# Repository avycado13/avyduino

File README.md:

# Avyduino

My take on the classic Arduino UNO. Powered by the same chips, but using a USB-C socket.

## Features
- USB-C
- Exact same pinout as classic Arduino UNO
- Power input switching
- Easy to solder components

## BOM
**FORGE REVIEWERS PLEASE ACTUALLY USE MY CSV**
I compiled 2 BOMs. One is from octopart and has parts sourced from multiple separate suppliers. [BOM here](ordering/bom.xlsx) and one entirely from LCSC. [BOM here](ordering/bom_lcsc_only.xlsx)

## Firmware
See [firmware/README.md](firmware/README.md) for the Uno Optiboot first-flash procedure and a USB serial bring-up sketch. The ATmega328P uses the standard Arduino Uno bootloader; the CH340G is a USB-to-UART bridge and does not need custom firmware.

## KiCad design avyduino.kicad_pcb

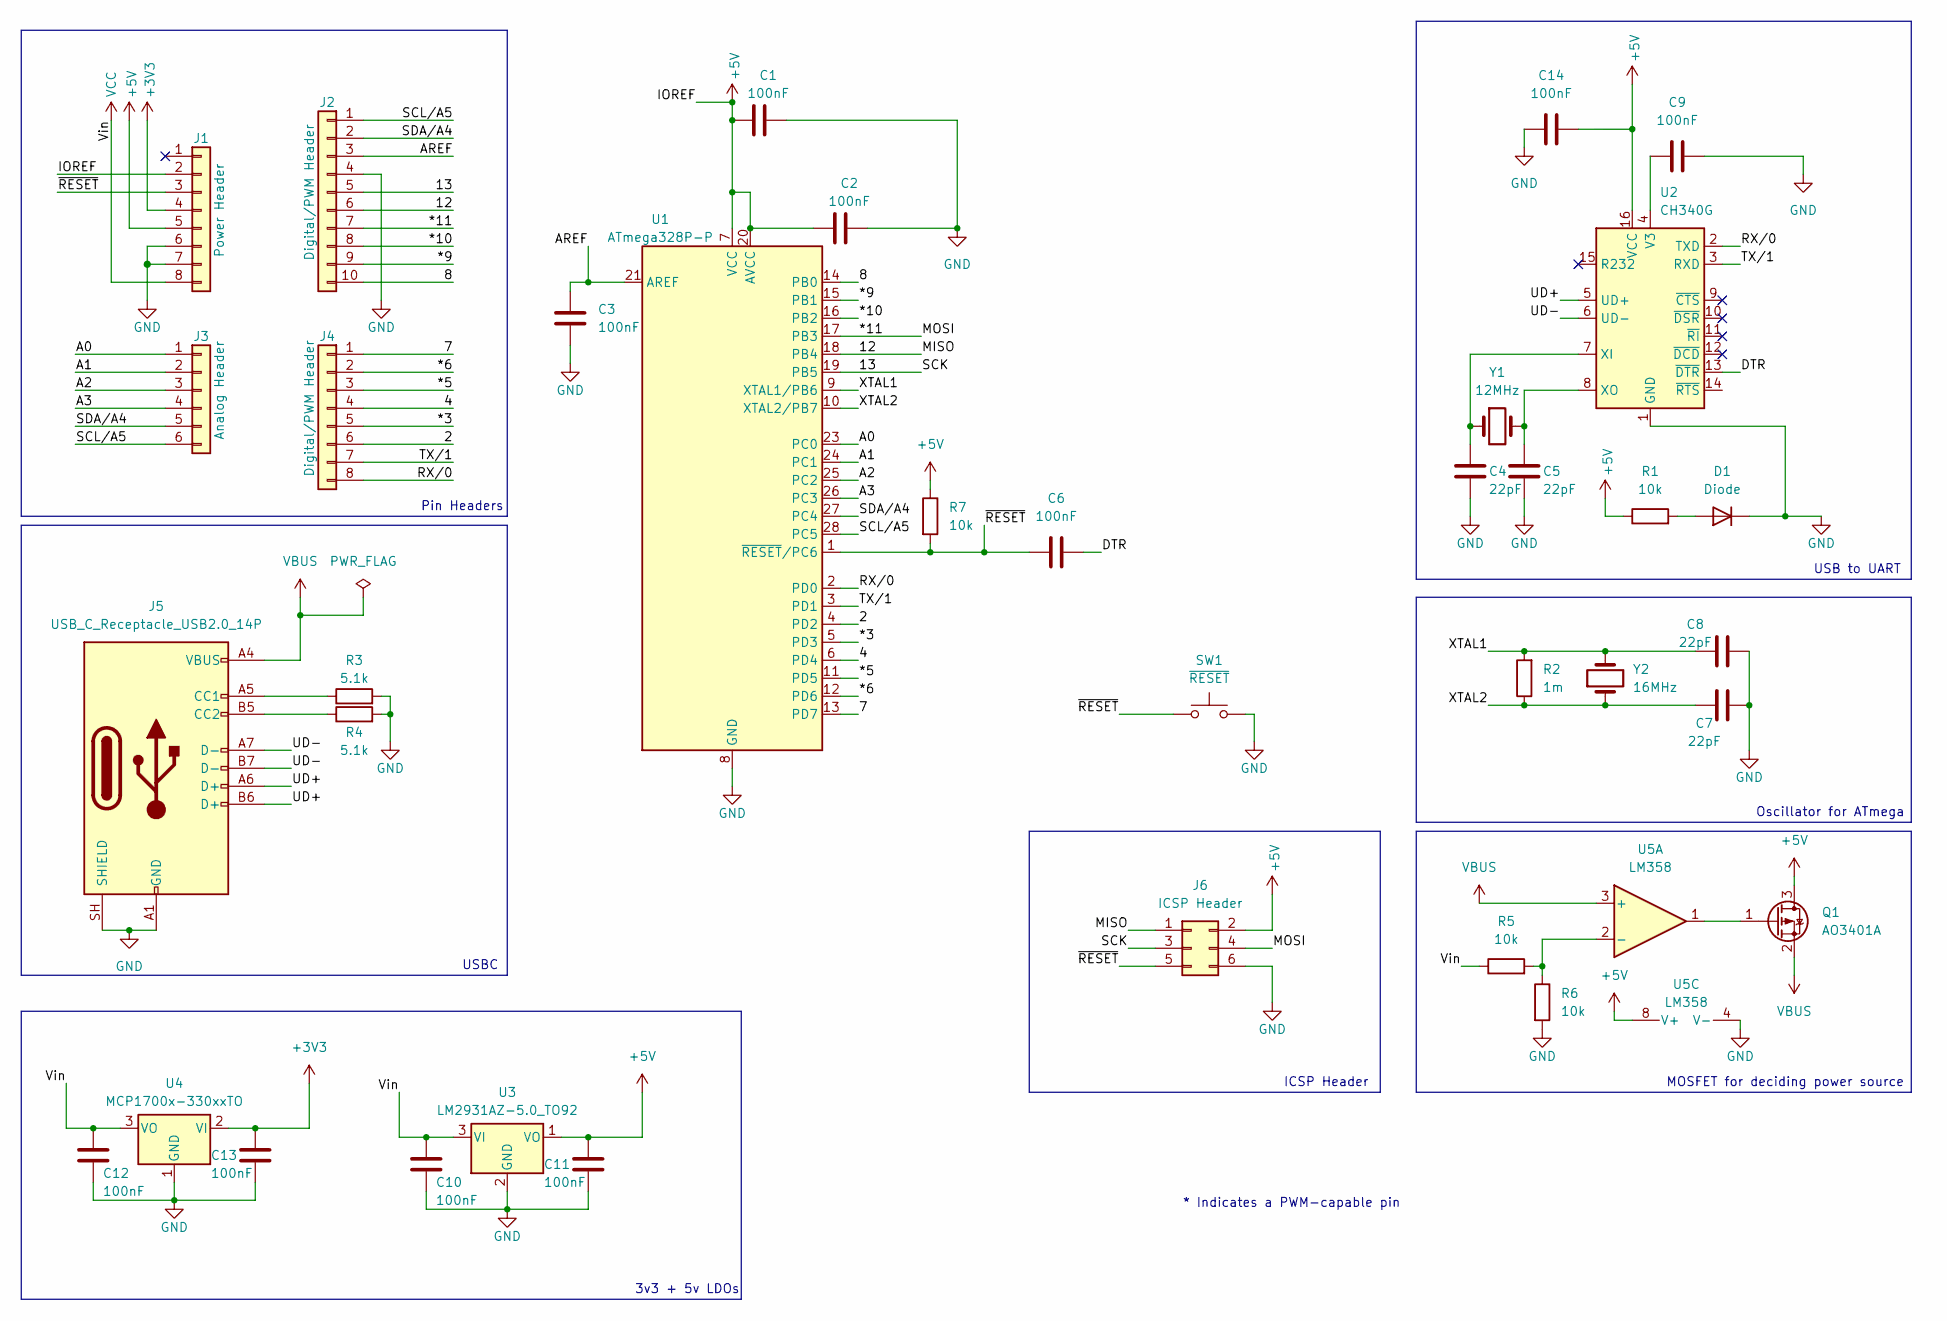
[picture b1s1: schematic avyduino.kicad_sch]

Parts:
C1, C2, C3, C6, C9, C10, C11, C12, C13, C14: 100nF; C_0805_2012Metric; MPN C0805C104K5RACTU
C4, C5, C7, C8: 22pF; C_0805_2012Metric; MPN C0805C220J5GACTU
D1: Diode; D_DO-35_SOD27_P10.16mm_Horizontal; MPN 1N4148
J1: Power Header; PinSocket_1x08_P2.54mm_Vertical; MPN SSW-108-01-T-S
J2: Digital/PWM Header; PinSocket_1x10_P2.54mm_Vertical; MPN SSW-110-01-T-S
J3: Analog Header; PinSocket_1x06_P2.54mm_Vertical; MPN SSW-106-01-T-S
J4: Digital/PWM Header; PinSocket_1x08_P2.54mm_Vertical; MPN SSW-108-01-T-S
J5: USB_C_Receptacle_USB2.0_14P; USB_C_Receptacle_GCT_USB4105-xx-A_16P_TopMnt_Horizontal; MPN SS-52400-002
J6: ICSP Header; PinHeader_2x03_P2.54mm_Vertical; MPN TSW-103-07-G-D
Q1: AO3401A; SOT-23; MPN AO3401A
R1, R5, R6: 10k; R_0805_2012Metric; MPN ERJ6ENF1002V
R2: 1m; R_0805_2012Metric; MPN AC0805FR-071ML
R3, R4: 5.1k; R_0805_2012Metric; MPN RC0805FR-075K1L
R7: 10k; R_0805_2012Metric_Pad1.20x1.40mm_HandSolder; MPN ERJ6ENF1002V
SW1: ~{RESET}; SW_PUSH_6mm
U1: ATmega328P-P; DIP-28_W7.62mm_Socket_LongPads; MPN ATMEGA328P-PU
U2: CH340G; SOIC-16_3.9x9.9mm_P1.27mm; MPN CH340G
U3: LM2931AZ-5.0_TO92; TO-92_Inline; MPN LM2931AZ-5.0RAG
U4: MCP1700x-330xxTO; TO-92_Inline; MPN MCP1700x-33002E/TO
U5: LM358; DIP-8_W7.62mm_Socket_LongPads; MPN LM358S-13
Y1: 12MHz; Crystal_HC49-U_Vertical; MPN ABLS2-12.000MHZ-D4Y-T
Y2: 16MHz; Crystal_HC49-U_Vertical; MPN ABM8G-16.000MHZ-18-D2Y-T

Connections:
+3V3: C13.2, J1.4, U4.2 (VI)
+5V: C1.1, C2.1, C11.2, C14.2, J1.2, J1.5, J6.2, Q1.3 (D), R1.1, R7.1, U1.7 (VCC), U1.20 (AVCC), U2.16 (VCC), U3.1 (VO), U5.8 (V+)
/2: J4.6, U1.4 (PD2)
/4: J4.4, U1.6 (PD4)
/7: J4.1, U1.13 (PD7)
/8: J2.10, U1.14 (PB0)
/12: J2.6, J6.1, U1.18 (PB4)
/13: J2.5, J6.3, U1.19 (PB5)
/*3: J4.5, U1.5 (PD3)
/*5: J4.3, U1.11 (PD5)
/*6: J4.2, U1.12 (PD6)
/*9: J2.9, U1.15 (PB1)
/*10: J2.8, U1.16 (PB2)
/*11: J2.7, J6.4, U1.17 (PB3)
/A0: J3.1, U1.23 (PC0)
/A1: J3.2, U1.24 (PC1)
/A2: J3.3, U1.25 (PC2)
/A3: J3.4, U1.26 (PC3)
/AREF: C3.1, J2.3, U1.21 (AREF)
/DTR: C6.2, U2.13 (~DTR)
/RX/0: J4.8, U1.2 (PD0), U2.2 (TXD)
/SCL/A5: J2.1, J3.6, U1.28 (PC5)
/SDA/A4: J2.2, J3.5, U1.27 (PC4)
/TX/1: J4.7, U1.3 (PD1), U2.3 (RXD)
/UD+: J5.A6 (D+), J5.B6 (D+), U2.5 (UD+)
/UD-: J5.A7 (D-), J5.B7 (D-), U2.6 (UD-)
/XTAL1: C8.1, R2.2, U1.9 (XTAL1/PB6), Y2.2
/XTAL2: C7.1, R2.1, U1.10 (XTAL2/PB7), Y2.1
/~RESET: C6.1, J1.3, J6.5, R7.2, SW1.1, U1.1 (~RESET/PC6)
GND: C1.2, C2.2, C3.2, C4.2, C5.2, C7.2, C8.2, C9.2, C10.1, C11.1, C12.1, C13.1, C14.1, D1.1 (K), J1.6, J1.7, J2.4, J5.A1 (GND), J5.A12 (GND), J5.B1 (GND), J5.B12 (GND), J5.SH (SHIELD), J6.6, R3.2, R4.2, R6.2, SW1.2, U1.8 (GND), U1.22 (GND), U2.1 (GND), U3.2 (GND), U4.1 (GND), U5.4 (V-)
unnamed: D1.2 (A), R1.2
unnamed: J5.A5 (CC1), R3.1
unnamed: J5.B5 (CC2), R4.1
unnamed: Q1.1 (G), U5.1
unnamed: C9.1, U2.4 (V3)
unnamed: C4.1, U2.7 (XI), Y1.1
unnamed: C5.1, U2.8 (XO), Y1.2
unnamed: R5.2, R6.1, U5.2 (-)
VBUS: J5.A4 (VBUS), J5.A9 (VBUS), J5.B4 (VBUS), J5.B9 (VBUS), Q1.2 (S), U5.3 (+)
VCC: C10.2, C12.2, J1.8, R5.1, U3.3 (VI), U4.3 (VO)

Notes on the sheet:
3v3 + 5v LDOs
ICSP Header
USB to UART
Pin Headers
MOSFET for deciding power source
* Indicates a PWM-capable pin
Oscillator for ATmega
USBC

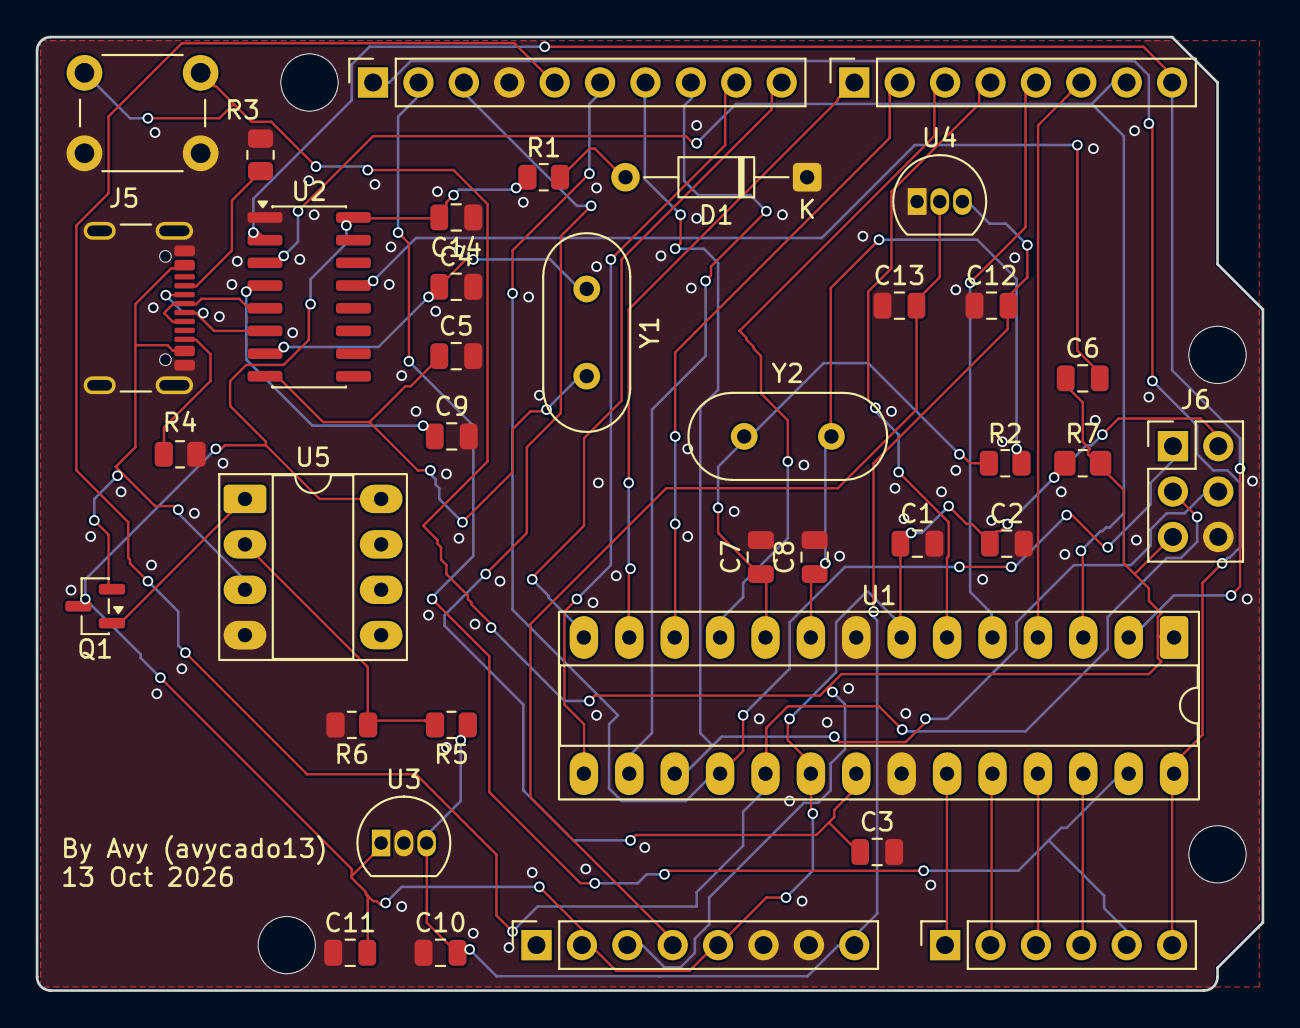
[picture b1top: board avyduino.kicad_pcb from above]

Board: 2 copper layers, 68.6 x 53.3 mm, 41 parts (0 on the bottom side), 40 nets.

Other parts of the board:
MH1, MH2, MH3, MH4: MountingHole_3.2mm

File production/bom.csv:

Designator,Footprint,Quantity,Value,LCSC Part #
"C1, C10, C11, C12, C13, C14, C2, C3, C6, C9",0805,10,100nF,C0805C104K5RACTU
"C4, C5, C7, C8",0805,4,22pF,C0805C220J5GACTU
D1,D_DO-35_SOD27_P10.16mm_Horizontal,1,Diode,1N4148
J1,PinSocket_1x08_P2.54mm_Vertical,1,Power Header,SSW-108-01-T-S
J2,PinSocket_1x10_P2.54mm_Vertical,1,Digital/PWM Header,SSW-110-01-T-S
J3,PinSocket_1x06_P2.54mm_Vertical,1,Analog Header,SSW-106-01-T-S
J4,PinSocket_1x08_P2.54mm_Vertical,1,Digital/PWM Header,SSW-108-01-T-S
J5,USB_C_Receptacle_GCT_USB4105-xx-A_16P_TopMnt_Horizontal,1,USB_C_Receptacle_USB2.0_14P,SS-52400-002
J6,PinHeader_2x03_P2.54mm_Vertical,1,ICSP Header, TSW-103-07-G-D
Q1,SOT-23,1,AO3401A,AO3401A
"R1, R5, R6, R7",0805,4,10k,ERJ6ENF1002V
R2,0805,1,1m,EE-SX953-W 1M
"R3, R4",0805,2,5.1k,RC0805FR-075K1L
U1,DIP-28_W7.62mm_Socket_LongPads,1,ATmega328P-P,ATMEGA328P-PU
U2,SOIC-16_3.9x9.9mm_P1.27mm,1,CH340G,CH340G
U3,TO-92_Inline,1,LM2931AZ-5.0_TO92,LM2931AZ-5.0RAG
U4,TO-92_Inline,1,MCP1700x-330xxTO,
U5,DIP-8_W7.62mm_Socket_LongPads,1,LM358,LM358S-13
Y1,Crystal_HC49-U_Vertical,1,12MHz,ABLS2-12.000MHZ-D4Y-T
Y2,Crystal_HC49-U_Vertical,1,16MHz,ABM8G-16.000MHZ-18-D2Y-T
